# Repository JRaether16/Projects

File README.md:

# Code done for ILVTE Summer 2017

RF-IR Remote: Software and schematic for RF-IR Remote. Remote received an RF transmitter signal and output an IR signal following the NEC1 protocol to an HDMI switcher.

Scripts: Software for camera scripts, mainly refactored code, as this was my first time doing any larger-scale programming.

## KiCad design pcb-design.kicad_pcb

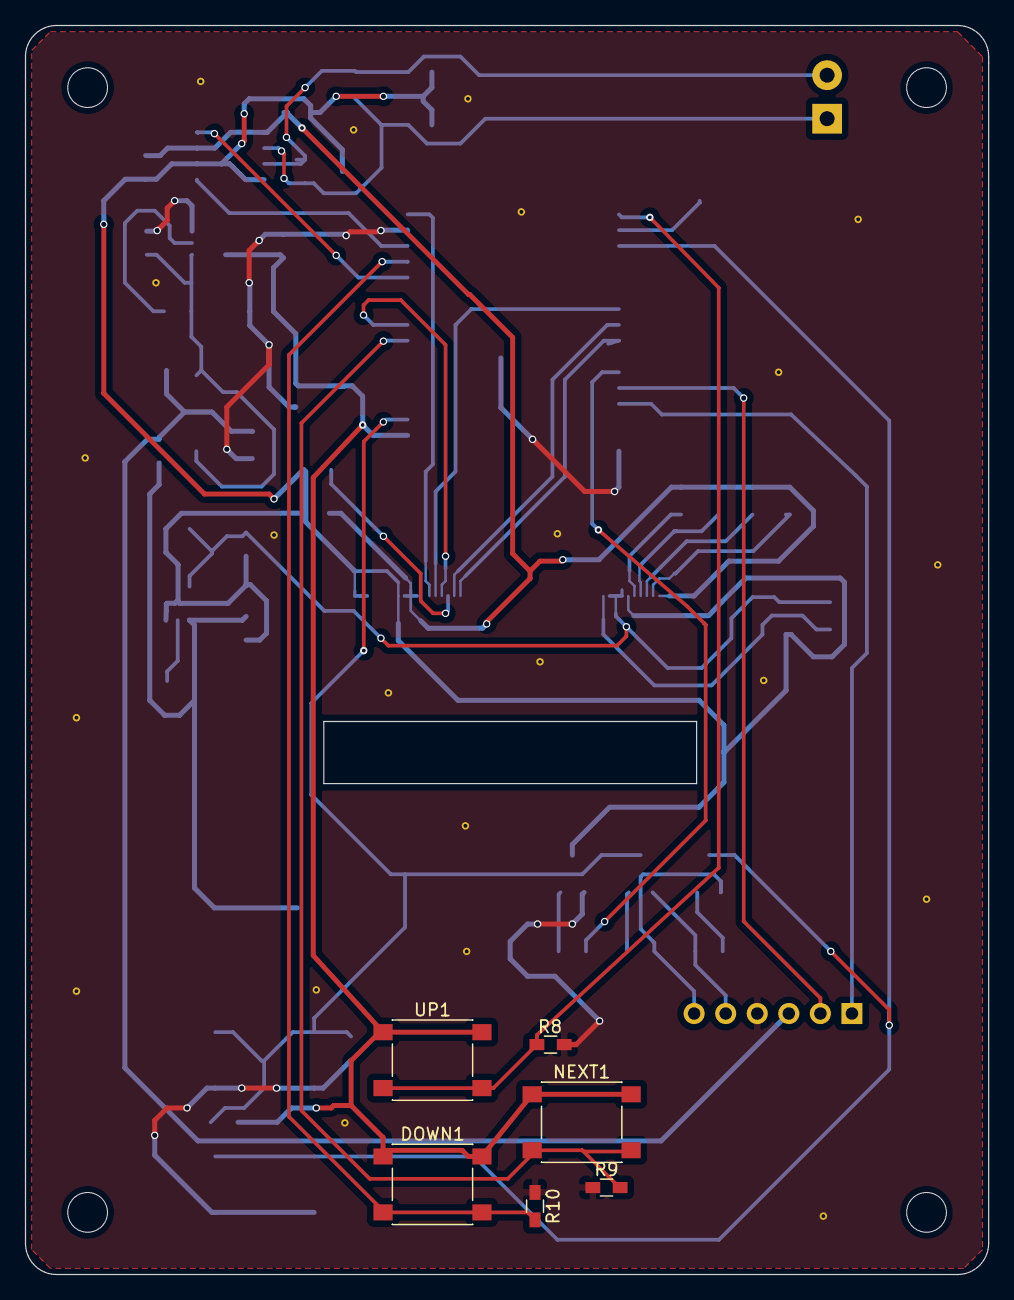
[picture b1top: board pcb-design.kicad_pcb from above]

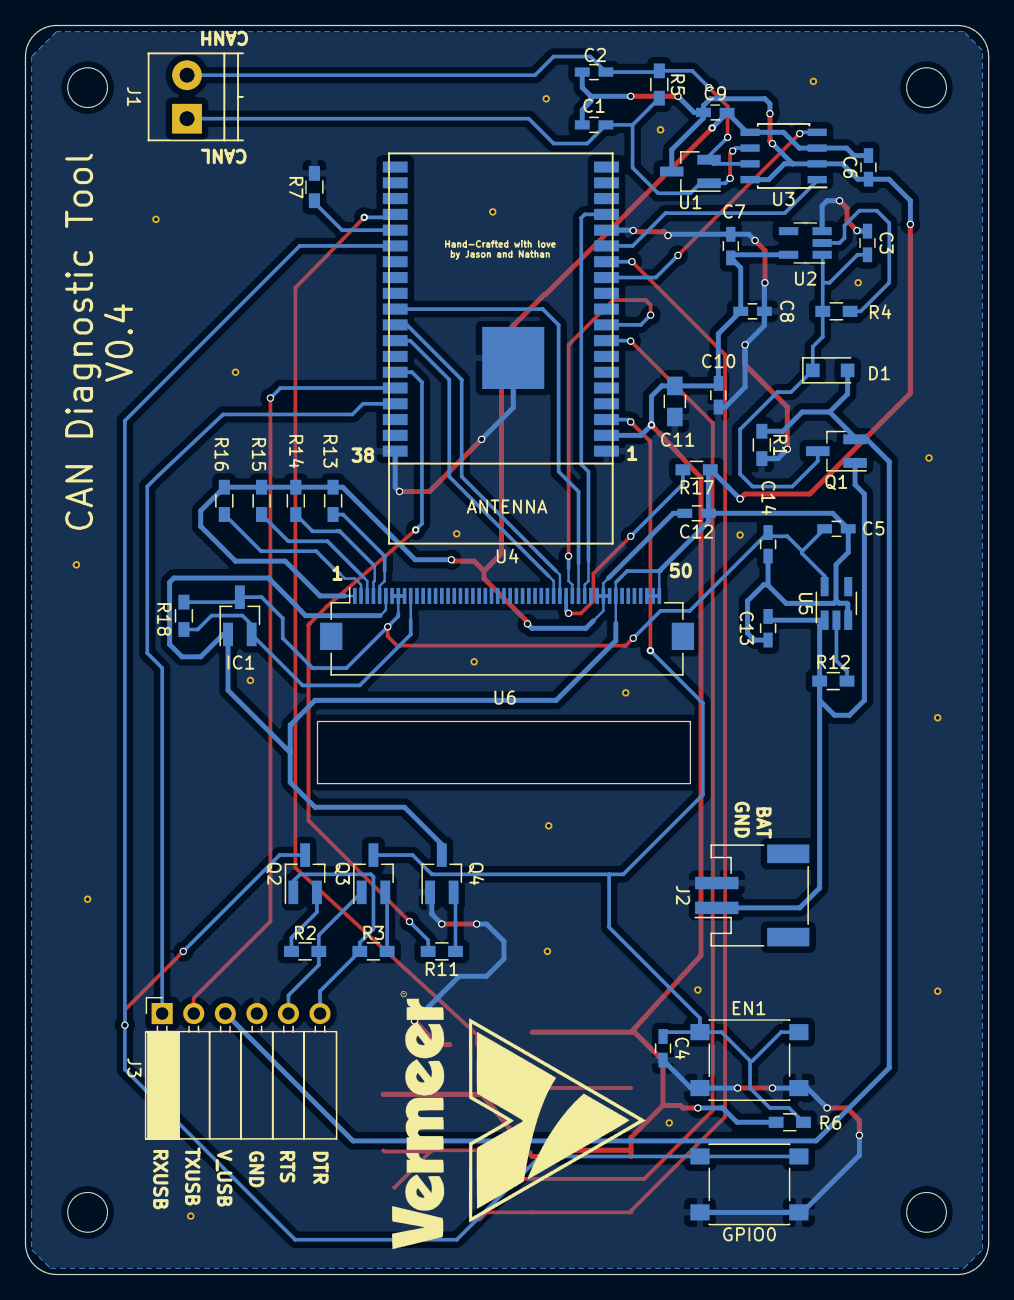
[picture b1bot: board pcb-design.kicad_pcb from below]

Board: 2 copper layers, 77.5 x 100.5 mm, 52 parts (46 on the bottom side), 39 nets.

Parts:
C1, C2: 22pF; C_0603_HandSoldering
C3, C5, C7, C13: 10uF; C_0603_HandSoldering
C4: 1nF; C_0603_HandSoldering
C6, C9, C12: 100nF; C_0603_HandSoldering
C8, C11, C14: 1uF; C_0603_HandSoldering
C10: 100uF; C_0805_HandSoldering
D1: D_Schottky; D_SOD-123F
DOWN1: SW_Push; SW_SPST_PTS645
EN1: SW_Push; SW_SPST_PTS645
GPIO0: SW_Push; SW_SPST_PTS645
IC1: APX803-SAG; SOT-23_Handsoldering
J1: CAN_TERMINAL; TerminalBlock_Phoenix_PT-3.5mm_2pol
J2: JST_CONN; JST_PH_S2B-PH-SM4-TB_02x2.00mm_Angled
J3: Conn_01x06_Female; Socket_Strip_Angled_1x06_Pitch2.54mm
NEXT1: SW_Push; SW_SPST_PTS645
Q1: Q_PMOS_DGS; SOT-23_Handsoldering
Q2, Q3, Q4: Q_NMOS_DGS; SOT-23_Handsoldering
R1, R4, R12: 100K; R_0603_HandSoldering
R2, R3, R8, R9, R10, R11, R17, R18: 10K; R_0603_HandSoldering
R5: 120; R_0603_HandSoldering
R6: 470; R_0603_HandSoldering
R7: 5K; R_0603_HandSoldering
R13, R14, R15, R16: 10; R_0603_HandSoldering
U1: AND8181/D; SOT-23_Handsoldering
U2, U5: AP2112-3.3; SOT-23-5_HandSoldering
U3: SN65HVD230; SOIC-8_3.9x4.9mm_Pitch1.27mm
U4: ESP32-WROVER
U6: MI0283QT-11; Hirose_FH12-50S-0.5SH_1x50-1MP_P0.50mm_Horizontal
UP1: SW_Push; SW_SPST_PTS645

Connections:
//STBY: R11.2, U4.33
/CANH: C2.2, J1.2, R5.1, U1.2, U3.7
/CANL: C1.2, J1.1, R5.2, U1.1, U3.6
/CE: U4.16, U6.38
/D/C: U4.9, U6.36
/DOWN: DOWN1.2, R10.2, U4.13
/DRV_IN: U3.1, U4.14
/EN: C4.1, EN1.2, Q3.3, R6.2, U4.3
/GPIO0: GPIO0.2, Q2.3, U4.25
/MISO: U4.31, U6.33
/MOSI: U4.30, U6.34
/NEXT: NEXT1.2, R9.2, U4.8
/RCV_OUT: U3.4, U4.12
/RXD0: J3.2, U4.34
/RXUSB: J3.1, U4.35
/SCK: U4.29, U6.37
/UP: R8.2, U4.23, UP1.2
DTR: J3.6, Q2.1, R3.1
GND: C3.2, C4.2, C7.2, C8.2, C10.2, C11.1, EN1.1, GPIO0.1, J2.2, J3.4, Q4.1, R1.2, R7.1, R8.1, R9.1, R10.1, U2.3, U4.1, U4.15, U4.38, U4.39
unnamed: C3.1, D1.1, Q1.3, R4.1, U2.1
unnamed: C5.2, C14.2, IC1.3, R18.1, U5.5, U6.7, U6.8, U6.9
unnamed: IC1.2, R18.2, U6.10
unnamed: Q2.2, R2.1
unnamed: Q3.2, R3.2
unnamed: Q4.2, R11.1
unnamed: R4.2, U2.2
unnamed: R7.2, U4.24
unnamed: R12.1, U5.2
unnamed: R13.1, U6.5
unnamed: R14.1, U6.4
unnamed: R15.1, U6.3
unnamed: R16.1, U6.2
unnamed: R17.2, U6.35
RTS: J3.5, Q3.1, R2.2
VCC: C6.2, C9.2, C12.2, R13.2, R14.2, R15.2, R16.2, U3.3, U3.5, U6.1, U6.40, U6.41, U6.42
VDD: C7.1, C8.1, C10.1, C11.2, DOWN1.1, NEXT1.1, R6.1, U2.5, U4.2, UP1.1
VSS: C1.1, C2.1, C5.1, C6.1, C9.1, C12.1, C13.2, C14.1, IC1.1, Q4.3, R17.1, U1.3, U3.2, U3.8, U5.3, U6.6, U6.43, U6.48, U6.49, U6.50
V_BAT: C13.1, J2.1, Q1.1, R12.2, U5.1
V_USB: D1.2, J3.3, Q1.2, R1.1

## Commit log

2017-09-18 Rename cameraclean.py to camera.py
2017-09-20 Create OnShape
2017-09-20 Rename OnShape to CAD
2017-09-20 Create foo
2017-09-20 Rename Receiver Schematic.brd to RF-IR Remote/Receiver Schematic.brd
2017-09-20 Rename RF-IR Remote/Receiver Schematic.brd to RF-IR Remote/Schematics/Receiver Schematic.brd
2017-09-20 Rename RF-IR Remote/Receiver Schematic.sch to RF-IR Remote/Schematics/Receiver Schematic.sch
2017-09-20 Rename RF-IR Remote/Transmission Schematic.brd to RF-IR Remote/Schematics/Transmission Schematic.brd
2017-09-20 Rename RF-IR Remote/Transmission Schematic.sch to RF-IR Remote/Remote/Transmission Schematic.sch
2017-09-20 Rename RF-IR Remote/Remote/Transmission Schematic.sch to RF-IR Remote/Schematics/RemoteTransmission Schematic.sch
2017-09-20 Rename RF-IR Remote/Remote_Reception.ino to RF-IR Remote/Arduino Code/Remote_Reception.ino
2017-09-20 Rename RF-IR Remote/Remote_Transmission.ino to RF-IR Remote/Arduino Code/Remote_Transmission.ino
2017-09-20 Rename OnShape to CAD Links/OnShape
2017-09-20 Rename camera.py to Scripts/camera.py
2017-09-20 Rename gps_logger.py to Scripts/gps_logger.py
2017-09-20 Rename mylog.py to Scripts/mylog.py
2017-09-20 Rename vte.sh to Scripts/vte.sh
2018-09-19 Added Robotics Vision project to Projects
2018-09-19 Added Robot Vision project to Projects
2019-01-11 Create Intern-Work
2020-09-11 removing vermeer stuff
2020-09-11 cleanup from root
